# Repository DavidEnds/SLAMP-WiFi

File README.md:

# SLAMP-WiFi
Version Wifi de la placa controladora SLAMP

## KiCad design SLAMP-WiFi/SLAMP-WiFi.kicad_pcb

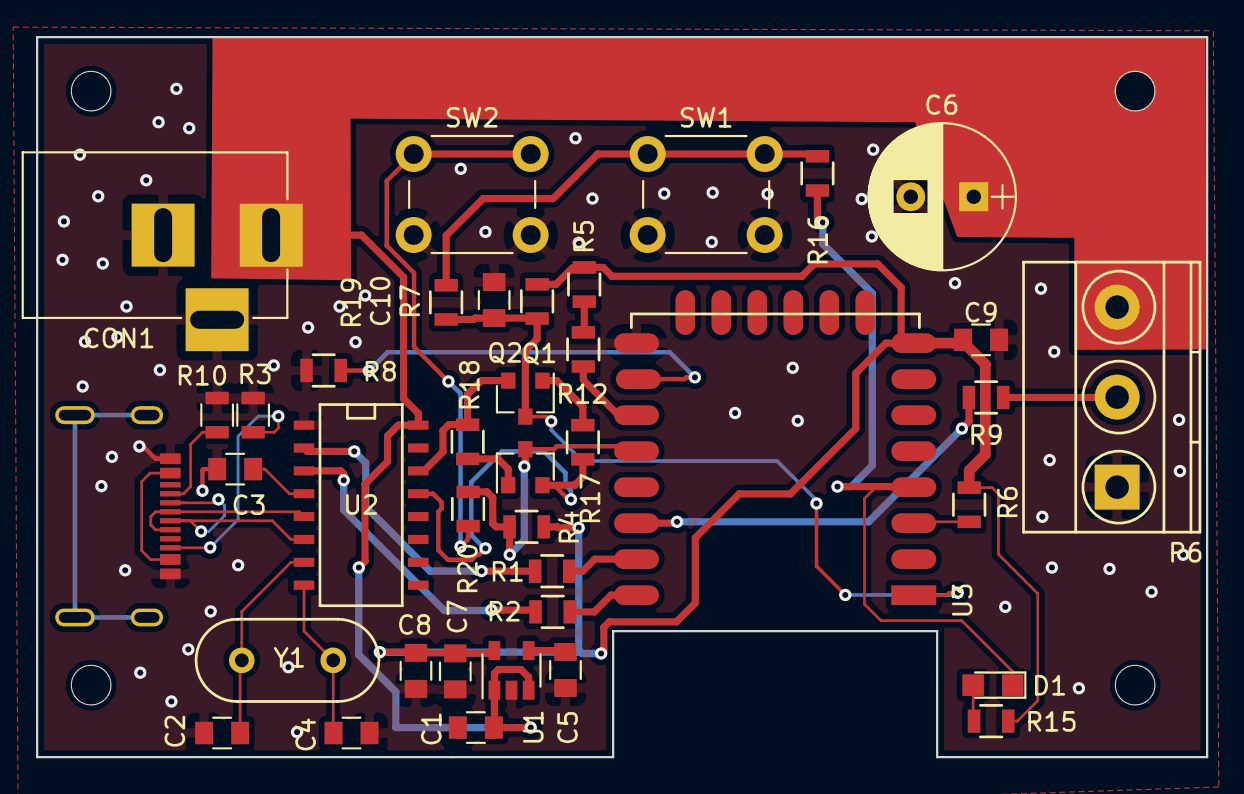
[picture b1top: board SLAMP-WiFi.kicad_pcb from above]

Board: 2 copper layers, 65.0 x 40.0 mm, 39 parts (0 on the bottom side), 32 nets.

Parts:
C1, C8: 1u; C_0805
C2, C4: 22p; C_0805
C3, C7: 100n; C_0805
C5, C10: 470p; C_0805
C6: 1000uF /6.3V; CP_Radial_D8.0mm_P3.50mm
C9: 100nF; C_0805
CON1: POWER_IN_5V; BARREL_JACK
D1: LED; LED_0805
P6: FACE1; TerminalBlock_Pheonix_MKDS1.5-3pol
Q1, Q2: S8050; SOT-23
R1, R2, R9, R12, R15, R16, R20: 470; R_0805
R3, R10: 5k1; R_0805
R4, R5, R6, R7, R8, R17, R18: 10k; R_0805
R19: 0 (NC); R_0805
SW1: KEY_RST; SW_PUSH_6mm
SW2: KEY_FLASH; SW_PUSH_6mm
U1: MIC5219-3.3BM5; SOT-23-5
U2: CH340G; SO-16-N
U3: ESP-12F; ESP-12E
USB1: HRO-TYPE-C-31-M-12; HRO-TYPE-C-31-M-13
Y1: 12 MHz; HC-49V

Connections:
3.3V: C7.1, C8.1, C9.1, R4.2, R5.2, R6.2, R7.2, R15.1, U1.5, U3.8
5V: C1.1, C6.1, CON1.1, P6.3, U1.1, U1.3, U2.16
D+: U2.5, USB1.6, USB1.8
D-: U2.6, USB1.5, USB1.7
DTR: Q2.2, R17.1, U2.13
EN: R6.1, U3.3
FACE1: P6.2, R9.1
FACE4: R5.1, R12.1
GND: C1.2, C2.2, C3.2, C4.2, C5.2, C6.2, C7.2, C8.2, C9.2, C10.2, CON1.2, CON1.3, P6.1, R3.2, R8.2, R10.2, SW1.2, SW2.2, U1.2, U2.1, U3.9, USB1.1, USB1.12
GPIO0: Q2.3, R4.1, R20.1, U3.12
GPIO15: R8.1, U3.10
GPIO16: D1.1, R16.1, U3.4
unnamed: C2.1, U2.7, Y1.1
unnamed: C3.1, U2.4
unnamed: C4.1, U2.8, Y1.2
unnamed: C5.1, U1.4
unnamed: D1.2, R15.2
unnamed: Q1.1, R17.2
unnamed: Q2.1, R18.2
unnamed: R1.1, U2.2
unnamed: R2.1, U2.3
unnamed: R3.1, USB1.10
unnamed: R9.2, U3.14
unnamed: R10.1, USB1.4
unnamed: R12.2, U3.11
unnamed: R16.2, R19.2, SW1.1
unnamed: R20.2, SW2.1
RTS: Q1.2, R18.1, U2.14
RXD: R2.2, U3.16
TXD: R1.2, U3.15
USB_5V: USB1.2, USB1.11
uRST: C10.1, Q1.3, R7.1, R19.1, U3.1

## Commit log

2017-06-05 Esquema empezado
2017-06-21 Comenzando el desarrollo del conversor USB-UART
2017-06-21 Desarrollo del conversor USB-UART terminado
2017-06-21 ADC terminado
2017-06-21 Pines de conexionado a las cara terminado, botones terminados
2017-06-21 Anotaciones y flags añadidos
2017-06-21 DRC pasado
2017-06-21 Simbolos asignados a sus huellas y netlist exportado
2017-07-01 layout terminado
2017-07-04 Serigrafia terminada
2017-07-04 Taladros añadidos
2017-07-09 Reparado error en el simbolo del transsitor S8050
2017-07-09 Serigrafia añadida y taladros cambiados
2017-07-09 Error con el GPIO0 arreglado
2018-02-25 Problema con los RTS solucionado
2018-03-11 Sensores tactiles añadidos
2018-03-12 mandada a fabrica
2021-05-23 actualizacion de archivos
2021-05-23 placa ionut terminada
